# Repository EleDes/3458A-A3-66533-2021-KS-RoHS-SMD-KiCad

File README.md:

# 3458A A3 ADC board replica in KiCad (66533 2021 KS RoHS SMD)

Based on CLIP 66503 and provided [pictures from recent 66533 version](Pictures/ "pictures from recent 66533 version").

There might be errors and there are a couple of open questions - [see issues](https://github.com/EleDes/3458A-A3-66533-2021-KS-RoHS-SMD-KiCad/issues/ "see issues")

If there are errors or questions please [open an issue](https://github.com/EleDes/3458A-A3-66533-2021-KS-RoHS-SMD-KiCad/issues/new).

[Schematics as pdf](3458A%20A3%2066533%202021%20KS%20SMD%20-%20Schematics.pdf?raw=true "Schematics as pdf")

[BOM (interactive)](https://htmlpreview.github.io/?https://github.com/EleDes/3458A-A3-66533-2021-KS-RoHS-SMD-KiCad/blob/main/ibom.html "BOM (interactive)")

[Gerbers](gerber_to_order/ "Gerbers")

[PCB as pdf](3458A%20A3%2066533%202021%20KS%20SMD%20-%20PCB.pdf?raw=true "PCB as pdf")

These 3D models are excluded from project license (folder 3D models):

0009483064: Molex KK 396 from [https://www.molex.com/en-us/products/part-detail/09483064](https://www.molex.com/en-us/products/part-detail/09483064) - copyright: Molex 

Avago HFBR: from [https://grabcad.com/library/avago-hfbr-0500etz-series-1](https://grabcad.com/library/avago-hfbr-0500etz-series-1) - terms of use: [https://blog.grabcad.com/terms-of-use/](https://blog.grabcad.com/terms-of-use/)

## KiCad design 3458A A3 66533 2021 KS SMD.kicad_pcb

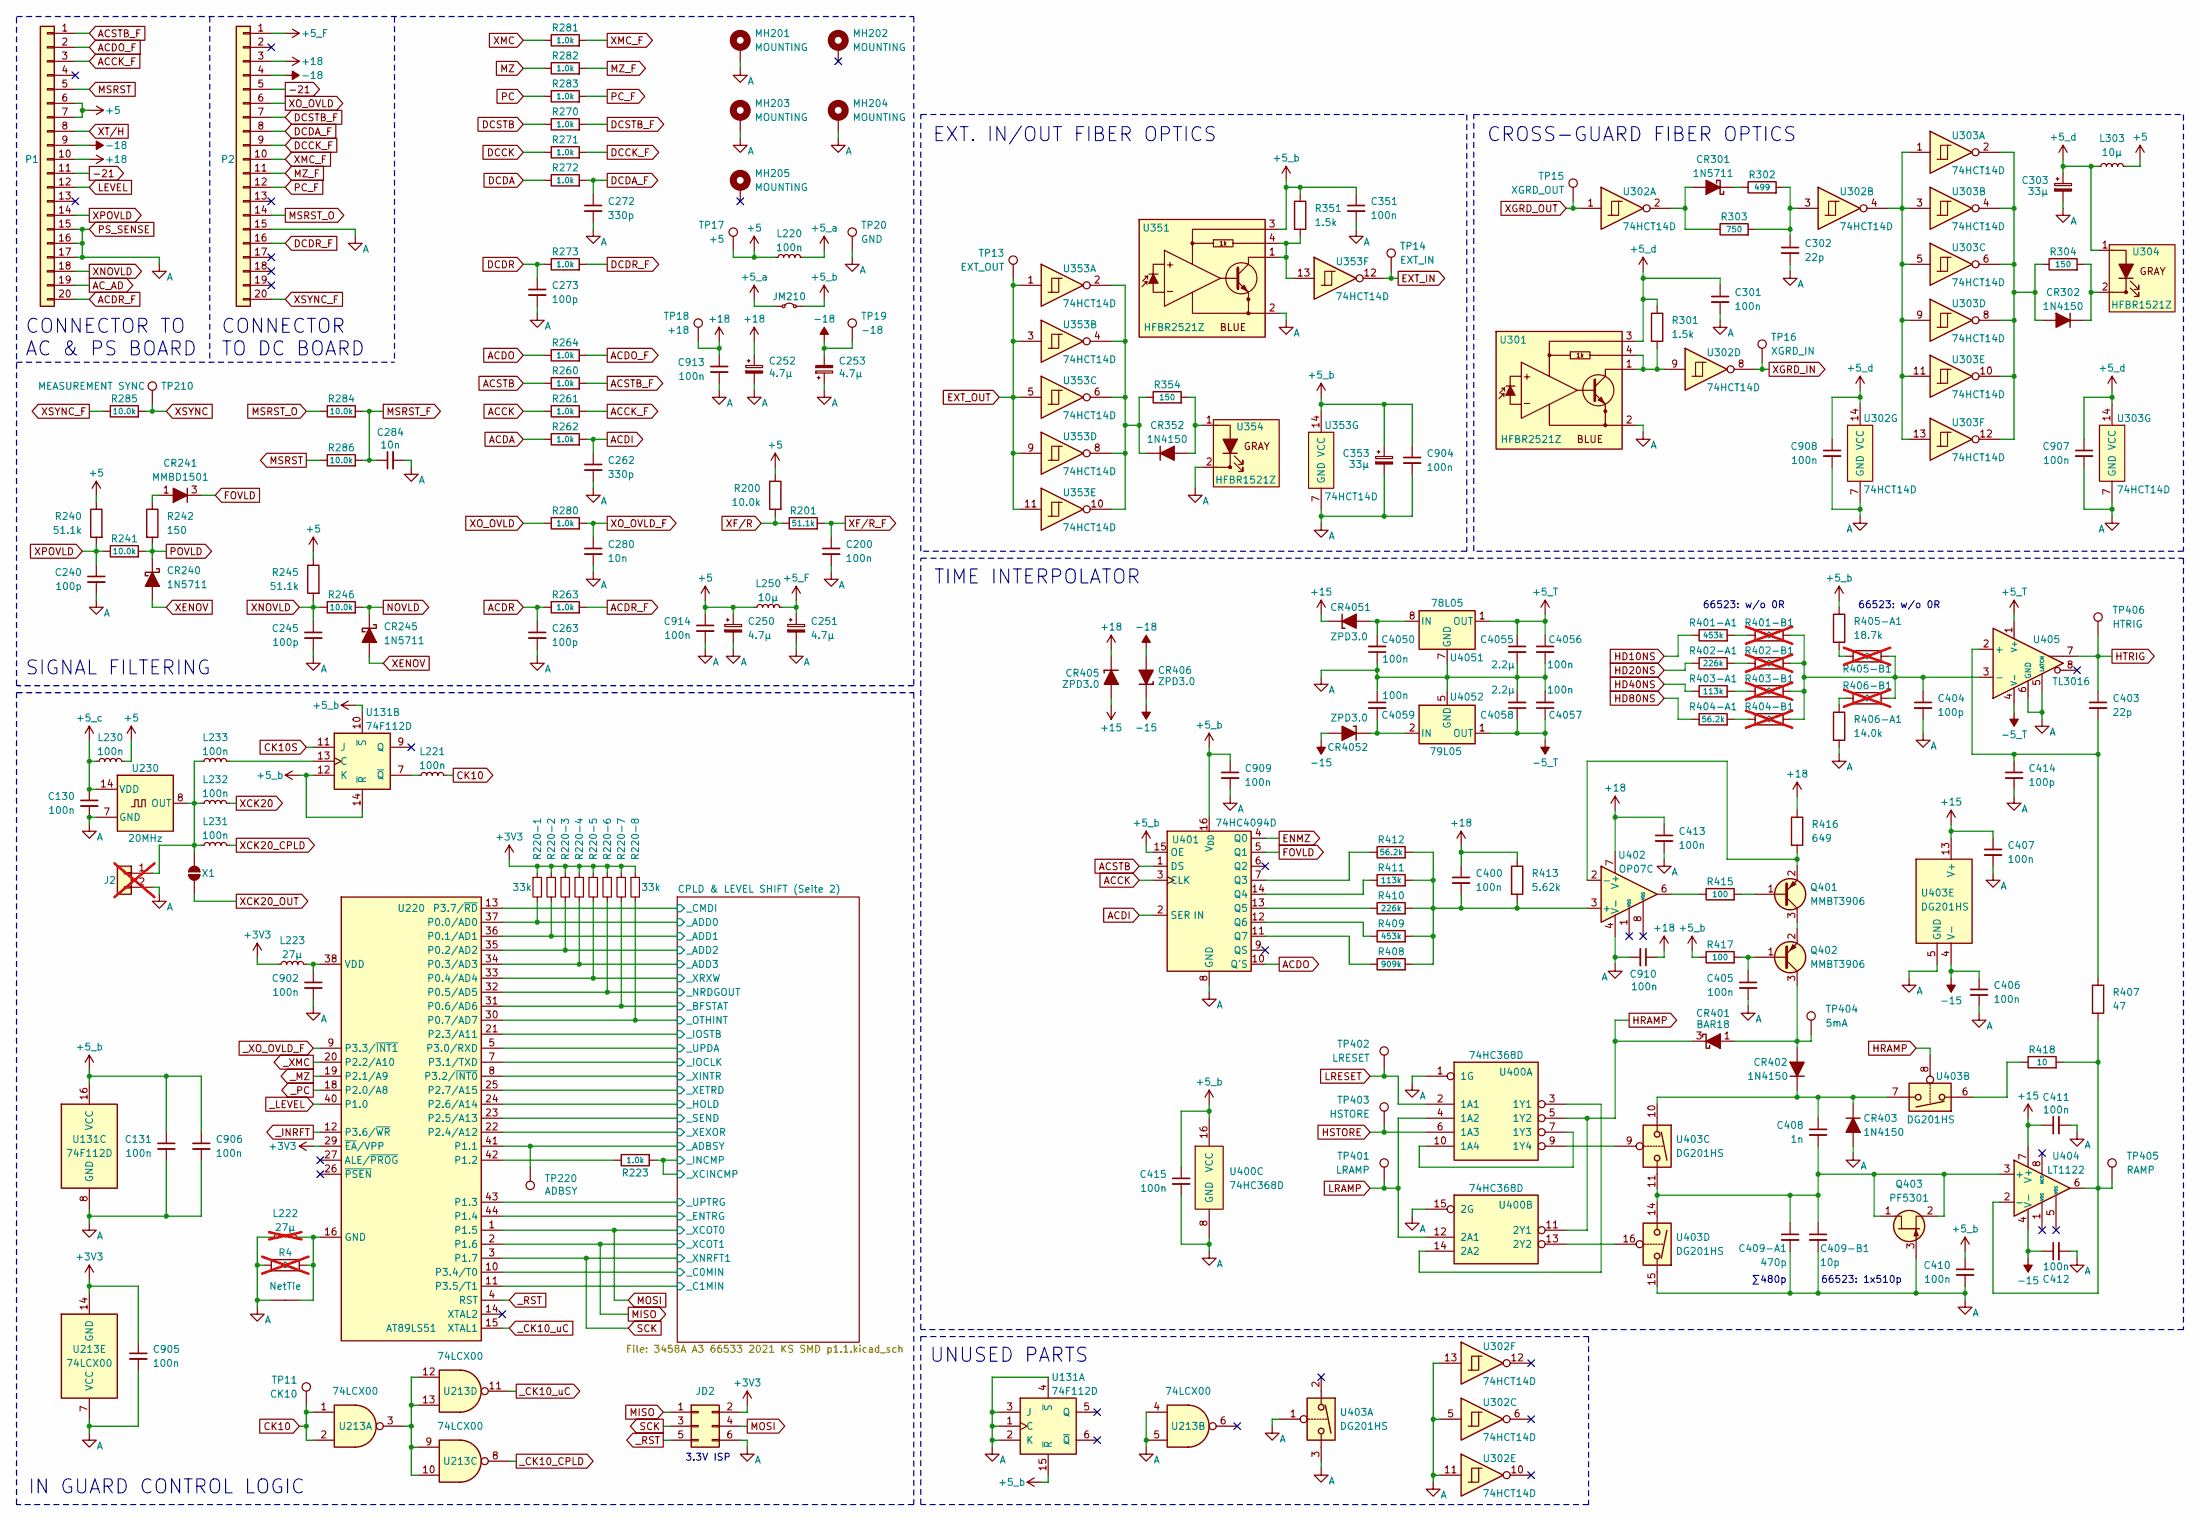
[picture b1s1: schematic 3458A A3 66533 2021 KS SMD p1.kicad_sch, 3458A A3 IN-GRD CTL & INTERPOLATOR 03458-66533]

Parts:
C130, C131, C200, C301, C351, C400, C405, C406, C410, C411, C412, C415, C902, C904, C905, C906, C907, C908, C909, C910, C913, C914, C4050, C4056, C4057, C4059: 100n; C_0603_1608Metric
C240, C245, C263, C273, C404, C414: 100p; C_0805_2012Metric
C250, C251, C252, C253: 4.7µ; CP_EIA-3528-21_Kemet-B
C262, C272: 330p; C_0603_1608Metric
C280, C284: 10n; C_0805_2012Metric
C302, C403: 22p; C_0603_1608Metric
C303, C353: 33µ; CP_EIA-3528-21_Kemet-B
C407, C413: 100n; C_0805_2012Metric
C408: 1n; C_0603_1608Metric
C409-A1: 470p; C_0603_1608Metric
C409-B1: 10p; C_0603_1608Metric
C4055, C4058: 2.2µ; C_0805_2012Metric
CR240, CR245, CR301: 1N5711; D_DO-35_SOD27_P7.62mm_Horizontal; Mfr. Part Number 1N5711
CR241: MMBD1501; SOT-23W; Mfr. Part Number MMBD1501
CR302, CR352, CR402, CR403: 1N4150; D_SOD-123; Mfr. Part Number 1N4150W
CR401: BAR18; SOT-23W; Mfr. Part Number BAR18
CR405, CR406, CR4051, CR4052: ZPD3.0; D_SOD-123; Mfr. Part Number MMSZ5225B
J2: Conn_01x02; PinHeader_1x02_P2.54mm_Vertical; not fitted
JD2: Conn_02x03; PinHeader_2x03_P2.54mm_Vertical
JM210: Jumper; R_1206_3216Metric
L220, L230, L231, L232, L233: 100n; L_0603_1608Metric
L221: 100n; L_0805_2012Metric
L222: 27µ; L_1812_4532Metric; not fitted
L223: 27µ; L_1812_4532Metric
L250, L303: 10µ; L_1812_4532Metric
MH201, MH202, MH203, MH204, MH205: MOUNTING; MountingHole_3.2mm_M3_Pad
P1, P2: Conn_01x20; IDC-Header_2x10_P2.54mm_Vertical; Mfr. Part Number 3592-6002
Q401, Q402: MMBT3906; SOT-23W; Mfr. Part Number MMBT3906
Q403: PF5301; TO-92_Inline_Wide_DSG; Mfr. Part Number PF5301
R4: 0; R_0603_1608Metric; not fitted
R200, R241, R246, R284, R285, R286: 10.0k; R_1206_3216Metric
R201, R240, R245: 51.1k; R_1206_3216Metric
R220-1, R220-2, R220-3, R220-4, R220-5, R220-6, R220-7, R220-8: 33k; R_0603_1608Metric
R223, R260, R261, R262, R263, R264, R270, R271, R272, R273, R280, R281, R282, R283: 1.0k; R_1206_3216Metric
R242, R304, R354: 150; R_1206_3216Metric
R301, R351: 1.5k; R_1206_3216Metric
R302: 499; R_0805_2012Metric
R303: 750; R_0805_2012Metric
R401-A1, R409: 453k; R_1206_3216Metric
R401-B1, R402-B1, R403-B1, R404-B1, R405-B1, R406-B1: 0; R_1206_3216Metric_Jumper_Closed; not fitted
R402-A1, R410: 226k; R_1206_3216Metric
R403-A1, R411: 113k; R_1206_3216Metric
R404-A1, R412: 56.2k; R_1206_3216Metric
R405-A1: 18.7k; R_1206_3216Metric
R406-A1: 14.0k; R_1206_3216Metric
R407: 47; R_1206_3216Metric
R408: 909k; R_1206_3216Metric
R413: 5.62k; R_1206_3216Metric
R415, R417: 100; R_1206_3216Metric
R416: 649; R_1206_3216Metric
R418: 10; R_1206_3216Metric
TIE1: NetTie; NetTie-2_SMD_Pad1mm; Part Number Do Not Place
TP11: CK10; TestPoint_THTPad_2.0x2.0mm_Drill1.0mm; Mfr. Part Number 16-06-0034
TP13: EXT_OUT; TestPoint_THTPad_2.0x2.0mm_Drill1.0mm; Mfr. Part Number 16-06-0034
TP14: EXT_IN; TestPoint_THTPad_2.0x2.0mm_Drill1.0mm; Mfr. Part Number 16-06-0034
TP15: XGRD_OUT; TestPoint_THTPad_2.0x2.0mm_Drill1.0mm; Mfr. Part Number 16-06-0034
TP16: XGRD_IN; TestPoint_THTPad_2.0x2.0mm_Drill1.0mm; Mfr. Part Number 16-06-0034
TP17: +5; TestPoint_THTPad_2.0x2.0mm_Drill1.0mm; Mfr. Part Number 16-06-0034
TP18: +18; TestPoint_THTPad_2.0x2.0mm_Drill1.0mm; Mfr. Part Number 16-06-0034
TP19: -18; TestPoint_THTPad_2.0x2.0mm_Drill1.0mm; Mfr. Part Number 16-06-0034
TP20: GND; TestPoint_THTPad_2.0x2.0mm_Drill1.0mm; Mfr. Part Number 16-06-0034
TP210: MEASUREMENT SYNC; TestPoint_THTPad_2.0x2.0mm_Drill1.0mm; Mfr. Part Number 16-06-0034
TP220: ADBSY; TestPoint_THTPad_2.0x2.0mm_Drill1.0mm; Mfr. Part Number 16-06-0034
TP401: LRAMP; TestPoint_THTPad_2.0x2.0mm_Drill1.0mm; Mfr. Part Number 16-06-0034
TP402: LRESET; TestPoint_THTPad_2.0x2.0mm_Drill1.0mm; Mfr. Part Number 16-06-0034
TP403: HSTORE; TestPoint_THTPad_2.0x2.0mm_Drill1.0mm; Mfr. Part Number 16-06-0034
TP404: 5mA; TestPoint_THTPad_2.0x2.0mm_Drill1.0mm; Mfr. Part Number 16-06-0034
TP405: RAMP; TestPoint_THTPad_2.0x2.0mm_Drill1.0mm; Mfr. Part Number 16-06-0034
TP406: HTRIG; TestPoint_THTPad_2.0x2.0mm_Drill1.0mm; Mfr. Part Number 16-06-0034
U131: 74F112D; SOIC-16_3.9x9.9mm_P1.27mm; Mfr. Part Number SN74F112D
U213: 74LCX00; SOIC-14_3.9x8.7mm_P1.27mm; Mfr. Part Number 74LCX00DG
U220: AT89LS51; TQFP-44_10x10mm_P0.8mm; Mfr. Part Number AT89LS51
U230: 20MHz; Oscillator_DIP-14; Mfr. Part Number M2014S132
U301, U351: HFBR2521Z; HFBR-2521Z Fiber Optic; Mfr. Part Number HFBR-2521Z
U302, U303, U353: 74HCT14D; SOIC-14_3.9x8.7mm_P1.27mm; Mfr. Part Number 74HCT14D
U304, U354: HFBR1521Z; HFBR-1521Z Fiber Optic; Mfr. Part Number HFBR1521Z
U400: 74HC368D; SOIC-16_3.9x9.9mm_P1.27mm; Mfr. Part Number 74HC368D
U401: 74HC4094D; SOIC-16_3.9x9.9mm_P1.27mm; Mfr. Part Number 74HC4094D
U402: OP07C; SOIC-8_3.9x4.9mm_P1.27mm; Mfr. Part Number OP07CDR
U403: DG201HS; SOIC-16_3.9x9.9mm_P1.27mm; Mfr. Part Number DG201HSDY
U404: LT1122; SOIC-8_3.9x4.9mm_P1.27mm; Mfr. Part Number LT1122CS8
U405: TL3016; SOIC-8_3.9x4.9mm_P1.27mm; Mfr. Part Number TL3016
U4051: 78L05; SOIC-8_3.9x4.9mm_P1.27mm; Mfr. Part Number MC78L05A
U4052: 79L05; SOIC-8_3.9x4.9mm_P1.27mm; Mfr. Part Number 79L05A
X1: Solder Jumper; SolderJumper-2_P1mm_Open_RoundedPad0.8x1.3mm

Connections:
+3V3: C905.1, JD2.2, L223.1, R220-1.1, R220-2.1, R220-3.1, R220-4.1, R220-5.1, R220-6.1, R220-7.1, R220-8.1, U213.14 (VCC), U220.29 (~EA/VPP); also elsewhere on the board
+5: C250.1, C914.1, L220.1, L230.2, L250.1, L303.2, P1.6, P1.7, R200.1, R240.1, R245.1, TP17.1; also elsewhere on the board
+5_F: C251.1, L250.2, P2.1; also elsewhere on the board
+5_T: C4055.1, C4056.1, U405.1 (V+), U4051.1 (OUT)
+5_a: JM210.1 (A), L220.2; also elsewhere on the board
+5_b: C131.1, C351.1, C353.1, C410.1, C415.1, C904.1, C906.1, C909.1, JM210.2 (B), R351.1, R405-A1.1, R417.1, U131.10 (~S), U131.12 (K), U131.14 (~R), U131.15 (~R), U131.16 (VCC), U351.3 (Vs), U353.14 (VCC), U400.16 (VCC), U401.15 (OE), U401.16 (V_{DD}); also elsewhere on the board
+5_c: C130.1, L230.1, U230.14 (VDD); also elsewhere on the board
+5_d: C301.1, C303.1, C907.1, C908.1, L303.1, R301.1, U301.3 (Vs), U302.14 (VCC), U303.14 (VCC), U304.1 (A)
+15: C407.1, C411.1, CR405.2 (A), CR4051.1 (K), U403.13 (V+), U404.7 (V+); also elsewhere on the board
+18: C252.1, C400.1, C413.1, C910.1, C913.1, CR405.1 (K), P1.10, P2.3, R413.1, R416.1, TP18.1, U402.7 (V+); also elsewhere on the board
-5_T: C4057.1, C4058.1, U405.4 (V-), U4052.1 (OUT)
-15: C406.1, C412.1, CR406.1 (K), CR4052.2 (A), U403.4 (V-), U404.4 (V-); also elsewhere on the board
-18: C253.2, CR406.2 (A), P1.9, P2.4, TP19.1; also elsewhere on the board
-21: P1.11, P2.5; also elsewhere on the board
/A3 IN-GRD CTL & INTERPOLATOR/CPLD & LEVEL SHIFT (Seite 2)/_ADBSY: TP220.1, U220.41 (P1.1); also elsewhere on the board
/A3 IN-GRD CTL & INTERPOLATOR/CPLD & LEVEL SHIFT (Seite 2)/_ADD0: R220-1.2, U220.37 (P0.0/AD0); also elsewhere on the board
/A3 IN-GRD CTL & INTERPOLATOR/CPLD & LEVEL SHIFT (Seite 2)/_ADD1: R220-2.2, U220.36 (P0.1/AD1); also elsewhere on the board
/A3 IN-GRD CTL & INTERPOLATOR/CPLD & LEVEL SHIFT (Seite 2)/_ADD2: R220-3.2, U220.35 (P0.2/AD2); also elsewhere on the board
/A3 IN-GRD CTL & INTERPOLATOR/CPLD & LEVEL SHIFT (Seite 2)/_ADD3: R220-4.2, U220.34 (P0.3/AD3); also elsewhere on the board
/A3 IN-GRD CTL & INTERPOLATOR/CPLD & LEVEL SHIFT (Seite 2)/_BFSTAT: R220-7.2, U220.31 (P0.6/AD6); also elsewhere on the board
/A3 IN-GRD CTL & INTERPOLATOR/CPLD & LEVEL SHIFT (Seite 2)/_C0MIN: U220.10 (P3.4/T0); also elsewhere on the board
/A3 IN-GRD CTL & INTERPOLATOR/CPLD & LEVEL SHIFT (Seite 2)/_C1MIN: U220.11 (P3.5/T1); also elsewhere on the board
/A3 IN-GRD CTL & INTERPOLATOR/CPLD & LEVEL SHIFT (Seite 2)/_CMDI: U220.13 (P3.7/~RD); also elsewhere on the board
/A3 IN-GRD CTL & INTERPOLATOR/CPLD & LEVEL SHIFT (Seite 2)/_ENTRG: U220.44 (P1.4); also elsewhere on the board
/A3 IN-GRD CTL & INTERPOLATOR/CPLD & LEVEL SHIFT (Seite 2)/_HOLD: U220.24 (P2.6/A14); also elsewhere on the board
/A3 IN-GRD CTL & INTERPOLATOR/CPLD & LEVEL SHIFT (Seite 2)/_INCMP: R223.2; also elsewhere on the board
/A3 IN-GRD CTL & INTERPOLATOR/CPLD & LEVEL SHIFT (Seite 2)/_IOCLK: U220.7 (P3.1/TXD); also elsewhere on the board
/A3 IN-GRD CTL & INTERPOLATOR/CPLD & LEVEL SHIFT (Seite 2)/_IOSTB: U220.21 (P2.3/A11); also elsewhere on the board
/A3 IN-GRD CTL & INTERPOLATOR/CPLD & LEVEL SHIFT (Seite 2)/_NRDGOUT: R220-6.2, U220.32 (P0.5/AD5); also elsewhere on the board
/A3 IN-GRD CTL & INTERPOLATOR/CPLD & LEVEL SHIFT (Seite 2)/_OTHINT: R220-8.2, U220.30 (P0.7/AD7); also elsewhere on the board
/A3 IN-GRD CTL & INTERPOLATOR/CPLD & LEVEL SHIFT (Seite 2)/_SEND: U220.23 (P2.5/A13); also elsewhere on the board
/A3 IN-GRD CTL & INTERPOLATOR/CPLD & LEVEL SHIFT (Seite 2)/_UPDA: U220.5 (P3.0/RXD); also elsewhere on the board
/A3 IN-GRD CTL & INTERPOLATOR/CPLD & LEVEL SHIFT (Seite 2)/_UPTRG: U220.43 (P1.3); also elsewhere on the board
/A3 IN-GRD CTL & INTERPOLATOR/CPLD & LEVEL SHIFT (Seite 2)/_XETRD: U220.25 (P2.7/A15); also elsewhere on the board
/A3 IN-GRD CTL & INTERPOLATOR/CPLD & LEVEL SHIFT (Seite 2)/_XEXOR: U220.22 (P2.4/A12); also elsewhere on the board
/A3 IN-GRD CTL & INTERPOLATOR/CPLD & LEVEL SHIFT (Seite 2)/_XINTR: U220.8 (P3.2/~INT0); also elsewhere on the board
/A3 IN-GRD CTL & INTERPOLATOR/CPLD & LEVEL SHIFT (Seite 2)/_XRXW: R220-5.2, U220.33 (P0.4/AD4); also elsewhere on the board
ACCK: R261.1, U401.3 (CLK); also elsewhere on the board
ACCK_F: P1.3, R261.2
ACDA: R262.1; also elsewhere on the board
ACDI: C262.1, R262.2, U401.2 (SER IN)
ACDO: R264.1, U401.10 (Q'S)
ACDO_F: P1.2, R264.2
ACDR: C263.1, R263.1; also elsewhere on the board
ACDR_F: P1.20, R263.2
ACSTB: R260.1, U401.1 (DS); also elsewhere on the board
ACSTB_F: P1.1, R260.2
AC_AD: P1.19; also elsewhere on the board
CK10: L221.2, TP11.1, U213.1, U213.2
CK10S: U131.11 (J); also elsewhere on the board
DCCK: R271.1; also elsewhere on the board
DCCK_F: P2.9, R271.2
DCDA: R272.1; also elsewhere on the board
DCDA_F: C272.1, P2.8, R272.2
DCDR: C273.1, R273.1; also elsewhere on the board
DCDR_F: P2.16, R273.2
DCSTB: R270.1; also elsewhere on the board
DCSTB_F: P2.7, R270.2
ENMZ: U401.4 (Q0); also elsewhere on the board
EXT_IN: TP14.1, U353.12; also elsewhere on the board
EXT_OUT: TP13.1, U353.1, U353.3, U353.5, U353.9, U353.11; also elsewhere on the board
FOVLD: CR241.3 (K), U401.5 (Q1)
GND: L222.2, R4.2, TIE1.2, U220.16 (GND), U220.17 (GND)
HD10NS: R401-A1.1; also elsewhere on the board
HD20NS: R402-A1.1; also elsewhere on the board
HD40NS: R403-A1.1; also elsewhere on the board
HD80NS: R404-A1.1; also elsewhere on the board
HRAMP: CR401.3 (K), U400.5 (1Y2), U400.11 (2Y1), U403.8
HSTORE: TP403.1, U400.6 (1A3); also elsewhere on the board
HTRIG: C403.1, TP406.1, U405.7; also elsewhere on the board
LEVEL: P1.12; also elsewhere on the board
LRAMP: TP401.1, U400.4 (1A2), U400.12 (2A1); also elsewhere on the board
LRESET: TP402.1, U400.2 (1A1); also elsewhere on the board
MISO: JD2.1, U220.2 (P1.6); also elsewhere on the board
MOSI: JD2.4, U220.1 (P1.5); also elsewhere on the board
MSRST: P1.5, R286.1
MSRST_F: C284.1, R284.2, R286.2; also elsewhere on the board
MSRST_O: P2.14, R284.1
MZ: R282.1; also elsewhere on the board
MZ_F: P2.11, R282.2
NOVLD: CR245.1 (K), R246.2; also elsewhere on the board
unnamed: C302.1, R302.2, R303.2, U302.3
unnamed: CR241.1 (A), R242.1
unnamed: CR301.2 (A), R303.1, U302.2
unnamed: CR301.1 (K), R302.1
unnamed: CR302.2 (A), R304.1, U303.2, U303.4, U303.6, U303.8, U303.10, U303.12
unnamed: CR302.1 (K), R304.2, U304.2 (K)
unnamed: CR352.2 (A), R354.2, U354.1 (A)
unnamed: CR352.1 (K), R354.1, U353.2, U353.4, U353.6, U353.8, U353.10
unnamed: CR401.1 (A), CR402.2 (A), Q402.3 (C), TP404.1
unnamed: C408.1, CR402.1 (K), CR403.1 (K), U403.7, U403.10
unnamed: C4050.2, CR4051.2 (A), U4051.8 (IN)
unnamed: C4059.2, CR4052.1 (K), U4052.2 (IN), U4052.3 (IN), U4052.6 (IN), U4052.7 (IN)
unnamed: J2.1, L231.1, L232.1, L233.1, U230.8 (OUT), X1.1 (A)
unnamed: Q401.1 (B), R415.2
unnamed: Q401.3 (C), Q402.2 (E)
unnamed: Q401.2 (E), R416.2, U402.2 (-)
unnamed: C405.1, Q402.1 (B), R417.2
unnamed: C408.2, C409-A1.1, C409-B1.1, Q403.1 (D), Q403.2 (S), U403.11, U403.14, U404.3 (+)
unnamed: R301.2, U301.1 (OUT), U301.4 (OUT), U302.9
unnamed: R351.2, U351.1 (OUT), U351.4 (OUT), U353.13
unnamed: R401-A1.2, R401-B1.1
unnamed: R402-A1.2, R402-B1.1
unnamed: R403-A1.2, R403-B1.1
unnamed: R404-A1.2, R404-B1.1
unnamed: R405-A1.2, R405-B1.1
unnamed: R406-A1.1, R406-B1.1
unnamed: R415.1, U402.6
unnamed: R418.1, U403.6
unnamed: L233.2, U131.13 (C)
unnamed: L221.1, U131.7 (~Q)
unnamed: U213.3, U213.9, U213.10, U213.12, U213.13
unnamed: R223.1, U220.42 (P1.2)
unnamed: C902.1, L223.2, U220.38 (VDD)
unnamed: U302.4, U303.1, U303.3, U303.5, U303.9, U303.11, U303.13
unnamed: U400.7 (1Y3), U400.10 (1A4)
unnamed: U400.3 (1Y1), U400.14 (2A2)
unnamed: U400.9 (1Y4), U403.9
unnamed: U400.13 (2Y2), U403.16
unnamed: R412.1, U401.7 (Q3)
unnamed: R411.1, U401.14 (Q4)
unnamed: R410.1, U401.13 (Q5)
unnamed: R409.1, U401.12 (Q6)
unnamed: R408.1, U401.11 (Q7)
unnamed: C400.2, R408.2, R409.2, R410.2, R411.2, R412.2, R413.2, U402.3 (+)
unnamed: R407.2, R418.2, TP405.1, U404.2 (-), U404.6
unnamed: C403.2, C414.1, R407.1, U405.2 (+)
unnamed: C404.1, R401-B1.2, R402-B1.2, R403-B1.2, R404-B1.2, R405-B1.2, R406-B1.2, U405.3 (-)
PC: R283.1; also elsewhere on the board
PC_F: P2.12, R283.2
POVLD: CR240.1 (K), R241.2, R242.2; also elsewhere on the board
PS_SENSE: C130.2, C131.2, C200.2, C240.2, C245.2, C250.2, C251.2, C252.2, C253.1, C262.2, C263.2, C272.2, C273.2, C280.2, C284.2, C301.2, C302.2, C303.2, C351.2, C353.2, C404.2, C405.2, C406.2, C407.2, C409-A1.2, C409-B1.2, C410.2, C411.2, C412.2, C413.2, C414.2, C415.2, C902.2, C904.2, C905.2, C906.2, C907.2, C908.2, C909.2, C910.2, C913.2, C914.2, C4050.1, C4055.2, C4056.2, C4057.2, C4058.2, C4059.1, CR403.2 (A), J2.2, JD2.6, L222.1, MH201.1, MH203.1, MH204.1, P1.15, P1.16, P1.17, P2.15, Q403.3 (G), R4.1, R406-A1.2, TIE1.1, TP20.1, U131.1 (C), U131.2 (K), U131.3 (J), U131.4 (~S), U131.8 (GND), U213.4, U213.5, U213.7 (GND), U230.7 (GND), U301.2 (GND), U302.5, U302.7 (GND), U302.11, U302.13, U303.7 (GND), U351.2 (GND), U353.7 (GND), U354.2 (K), U400.1 (1G), U400.8 (GND), U400.15 (2G), U401.8 (GND), U402.4 (V-), U403.1, U403.3, U403.5 (GND), U403.15, U405.5 (LATCH), U405.6 (GND), U4051.2 (GND), U4051.3 (GND), U4051.6 (GND), U4051.7 (GND), U4052.5 (GND); also elsewhere on the board
SCK: JD2.3, U220.3 (P1.7); also elsewhere on the board
XCK20: L232.2; also elsewhere on the board
XCK20_CPLD: L231.2; also elsewhere on the board
XCK20_OUT: X1.2 (B); also elsewhere on the board
XENOV: CR240.2 (A), CR245.2 (A); also elsewhere on the board
XF/R: R200.2, R201.1; also elsewhere on the board
XF/R_F: C200.1, R201.2; also elsewhere on the board
XGRD_IN: TP16.1, U302.8; also elsewhere on the board
XGRD_OUT: TP15.1, U302.1; also elsewhere on the board
XMC: R281.1; also elsewhere on the board
XMC_F: P2.10, R281.2
XNOVLD: C245.1, P1.18, R245.2, R246.1
XO_OVLD: P2.6, R280.1
XO_OVLD_F: C280.1, R280.2; also elsewhere on the board
XPOVLD: C240.1, P1.14, R240.2, R241.1
XSYNC: R285.2, TP210.1; also elsewhere on the board
XSYNC_F: P2.20, R285.1
XT/H: P1.8; also elsewhere on the board
_CK10_CPLD: U213.8; also elsewhere on the board
_CK10_uC: U213.11, U220.15 (XTAL1)
_INRFT: U220.12 (P3.6/~WR); also elsewhere on the board
_LEVEL: U220.40 (P1.0); also elsewhere on the board
_MZ: U220.19 (P2.1/A9); also elsewhere on the board
_PC: U220.18 (P2.0/A8); also elsewhere on the board
_RST: JD2.5, U220.4 (RST); also elsewhere on the board
_XMC: U220.20 (P2.2/A10); also elsewhere on the board
_XO_OVLD_F: U220.9 (P3.3/~INT1); also elsewhere on the board

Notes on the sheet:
66523: w/o 0R
IN GUARD CONTROL LOGIC
CONNECTOR TO DC BOARD
CONNECTOR TO AC & PS BOARD
CROSS-GUARD FIBER OPTICS
∑480p
UNUSED PARTS
TIME INTERPOLATOR
66523: 1x510p
SIGNAL FILTERING
3.3V ISP
EXT. IN/OUT FIBER OPTICS
